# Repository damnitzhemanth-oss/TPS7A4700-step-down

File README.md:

# TPS7A4700-step-down.

## 1. Project Overview 

This is an breakout board for TPS7A4700 module. 

### How it works?

This module contains several pins like 6V2,0V2,0V4.., when connected to GND it adds the respective voltage to the OUT.

### Why I built this?

When I was designing [FusionBoard](https://github.com/damnitzhemanth-oss/FusionBoard), I was really fascinated with this board. And I wanted to design a breakout board for this.

## 2. Specifications 

| Parameter | TPS7A4700 |
|---|---:|
| Device type | Positive high-voltage, ultralow-noise LDO linear regulator |
| Input voltage range | +3 V to +36 V |
| Recommended operating input voltage | 3.0 V to 35.0 V |
| Output voltage mode | ANY-OUT user-programmable via PCB layout |
| Output voltage range | +1.4 V to +20.5 V |
| Adjustable output mode | Not applicable |
| Output current | 1 A |
| Output voltage step size | 100 mV |
| Reference voltage | 1.4 V |
| Dropout voltage | 307 mV at 1 A |
| Output noise | 4 µV_RMS (10 Hz to 100 kHz) |
| PSRR | 82 dB at 100 Hz; ≥55 dB (10 Hz to 10 MHz) |
| Enable pin | CMOS logic-level compatible |
| Protection | Built-in fixed current limit and thermal shutdown |
| Thermal shutdown temperature | ~170°C shutdown; ~150°C reset |
| Operating junction temperature | -40°C to 125°C |
| Package | VQFN-20, 5 mm × 5 mm |

Checkout [Datasheet](Datasheets/TPS7A4700.pdf) for more details.

### Pin Setting

| Vo (V) | 0P1V<br>100 mV | 0P2V<br>200 mV | 0P4V<br>400 mV | 0P8V<br>800 mV | 1P6V<br>1.6 V | 3P2V<br>3.2 V | 6P4V1<br>6.4 V | 6P4V2<br>6.4 V |
| :---: | :---: | :---: | :---: | :---: | :---: | :---: | :---: | :---: |
| 1.4 | Open | Open | Open | Open | Open | Open | Open | Open |
| 1.5 | GND | Open | Open | Open | Open | Open | Open | Open |
| 1.8 | Open | Open | GND | Open | Open | Open | Open | Open |
| 2.5 | GND | GND | Open | GND | Open | Open | Open | Open |
| 3 | Open | Open | Open | Open | GND | Open | Open | Open |
| 3.3 | GND | GND | Open | Open | GND | Open | Open | Open |
| 4.5 | GND | GND | GND | GND | GND | Open | Open | Open |
| 5 | Open | Open | GND | Open | Open | GND | Open | Open |
| 10 | Open | GND | GND | Open | GND | Open | GND | Open |
| 12 | Open | GND | Open | GND | Open | GND | GND | Open |
| 15 | Open | Open | Open | GND | Open | Open | GND | GND |
| 18 | Open | GND | GND | Open | Open | GND | GND | GND |
| 20.5 | GND | GND | GND | GND | GND | GND | GND | GND |

## 3. Bill of Materials (BoM)

| Id | Designator | Footprint | Quantity | Designation | Supplier and ref |
|---|---|---|---|---|---|
| 1 | C1, C2 | C_0805_2012Metric | 2 | 10uF | |
| 2 | C3 | C_0805_2012Metric | 1 | 47uF | |
| 3 | J1 | PinHeader_1x02_P2.54mm_Vertical | 1 | Ground/Power | |
| 4 | J2 | PinHeader_1x02_P2.54mm_Vertical | 1 | 6P4V2 | |
| 5 | J3 | PinHeader_1x02_P2.54mm_Vertical | 1 | 6P4V1 | |
| 6 | J4 | PinHeader_1x02_P2.54mm_Vertical | 1 | 3P2V | |
| 7 | J5 | PinHeader_1x02_P2.54mm_Vertical | 1 | 1P6V | |
| 8 | J6 | PinHeader_1x02_P2.54mm_Vertical | 1 | 0P8V | |
| 9 | J7 | PinHeader_1x02_P2.54mm_Vertical | 1 | 0P4V | |
| 10 | J8 | PinHeader_1x02_P2.54mm_Vertical | 1 | 0P1V | |
| 11 | J9 | PinHeader_1x02_P2.54mm_Vertical | 1 | 0PV2 | |
| 12 | OUT + 1 | PinHeader_1x01_P2.54mm_Vertical | 1 | Out Pin | |
| 13 | TP1 | TestPoint_Pad_D1.5mm | 1 | + Pad | |
| 14 | TP2 | TestPoint_Pad_D1.5mm | 1 | Ground Pad | |
| 15 | TP3 | TestPoint_Pad_D1.5mm | 1 | Out Pad | |
| 16 | U1 | VQFN-20_L5.0-W5.0-P0.65-TL-EP | 1 | TPS7A4700RGWR | |

Check [Interactive-BOM](Production/BOM/ibom.html) for more insights.

## 4. Repo Navigation

```
TPS7A4700-step-down
├── CAD
│   └── STEP_DOWN.step
├── Datasheets
│   └── TPS7A4700.pdf
├── Images
│   ├── DRC.png
│   ├── PCB3D.png
│   ├── PCB_H.png
│   └── Pin_Settings.png
├── LICENSE
├── Production
│   ├── BOM
│   │   ├── STEP_DOWN.csv
│   │   └── ibom.html
│   ├── Gerbers
│   │   ├── STEP_DOWN_47.99x31.08mm_for_Default.zip
│   │   ├── STEP_DOWN_47.99x31.08mm_for_Elecrow.zip
│   │   ├── STEP_DOWN_47.99x31.08mm_for_FusionPCB.zip
│   │   ├── STEP_DOWN_47.99x31.08mm_for_JLCPCB.zip
│   │   └── STEP_DOWN_47.99x31.08mm_for_PCBWay.zip
│   └── STEP_DOWN-all-pos.csv
├── README.md
└── STEP_DOWN
    ├── STEP_DOWN.kicad_pcb
    ├── STEP_DOWN.kicad_pro
    └── STEP_DOWN.kicad_sch
```

## 5. Credits 

- [KiCad](https://www.google.com/url?opi=89978449&q=https://www.kicad.org/&sa=U&ved=2ahUKEwimlZP32eWXAxW-jOEIHdIBCzUQFnoECBEQAQ&usg=AOvVaw3RWTRyOBHwgJWf9Tp2GrV8), used as cad.
- [easyeda2kicad](https://github.com/BiggiePete/easyeda2kicad-App) extension for downloading footprint,symbols, 3d models.
- Interactive BOM Plugin.
- Round Corners Plugin.

## 7. Gallery

### PCB 

### 3D

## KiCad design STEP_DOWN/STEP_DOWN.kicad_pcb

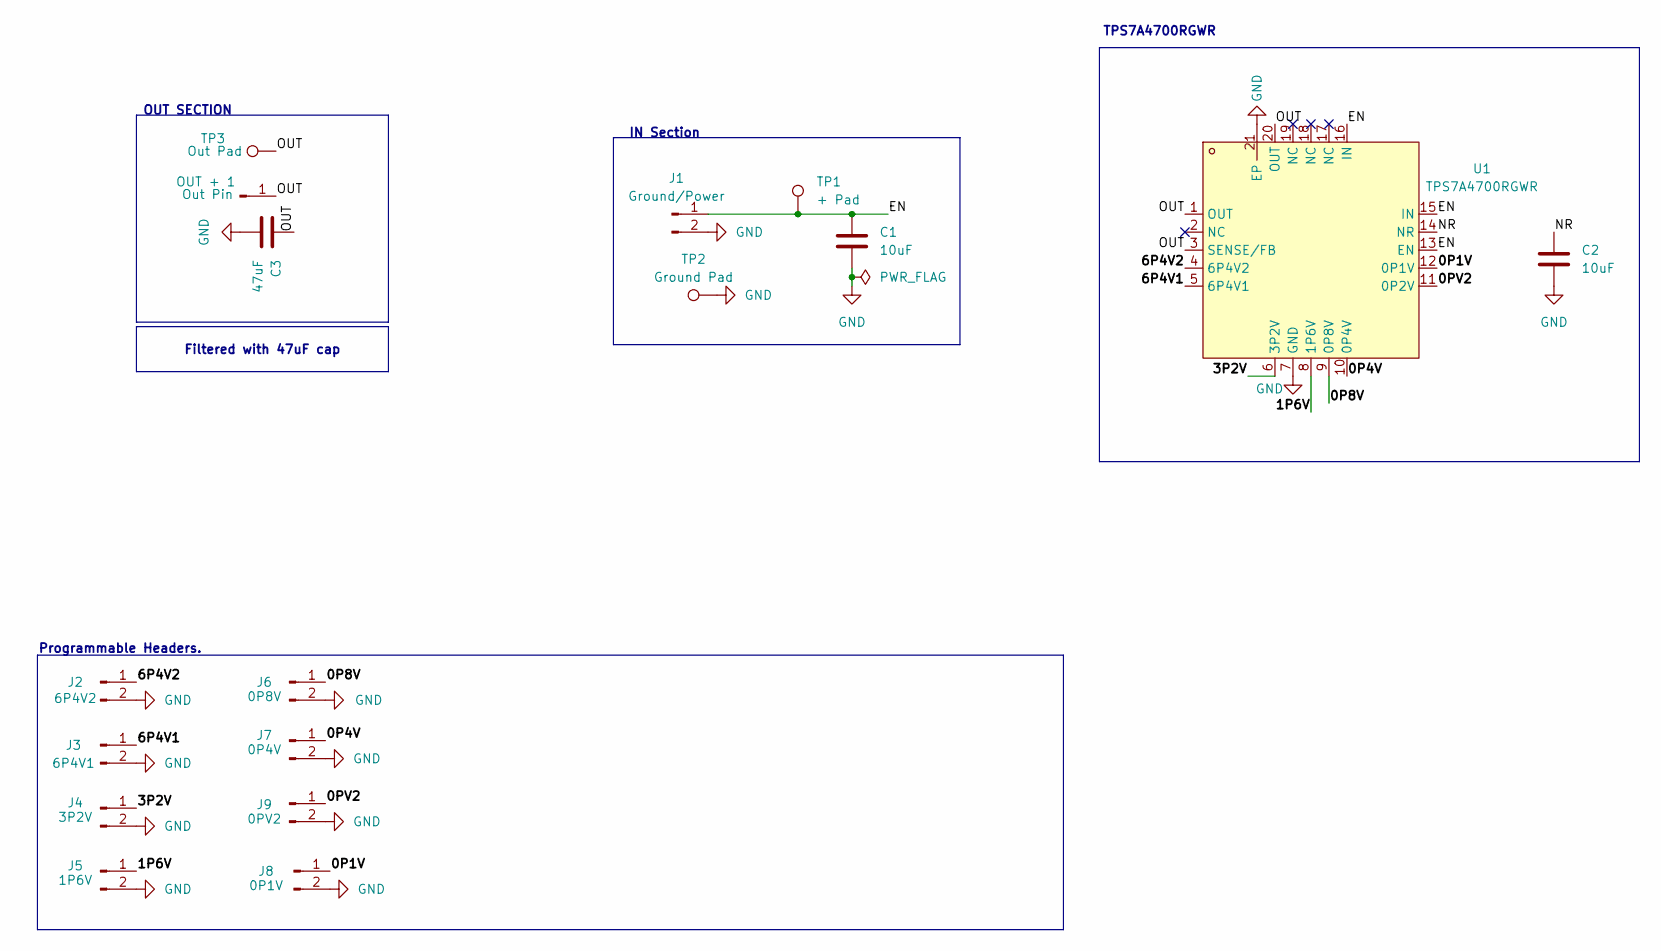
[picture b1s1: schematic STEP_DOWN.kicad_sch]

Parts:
C1, C2: 10uF; C_0805_2012Metric
C3: 47uF; C_0805_2012Metric
J1: Ground/Power; PinHeader_1x02_P2.54mm_Vertical
J2: 6P4V2; PinHeader_1x02_P2.54mm_Vertical
J3: 6P4V1; PinHeader_1x02_P2.54mm_Vertical
J4: 3P2V; PinHeader_1x02_P2.54mm_Vertical
J5: 1P6V; PinHeader_1x02_P2.54mm_Vertical
J6: 0P8V; PinHeader_1x02_P2.54mm_Vertical
J7: 0P4V; PinHeader_1x02_P2.54mm_Vertical
J8: 0P1V; PinHeader_1x02_P2.54mm_Vertical
J9: 0PV2; PinHeader_1x02_P2.54mm_Vertical
OUT + 1: Out Pin; PinHeader_1x01_P2.54mm_Vertical
TP1: + Pad; TestPoint_Pad_D1.5mm
TP2: Ground Pad; TestPoint_Pad_D1.5mm
TP3: Out Pad; TestPoint_Pad_D1.5mm
U1: TPS7A4700RGWR; VQFN-20_L5.0-W5.0-P0.65-TL-EP; MPN TPS7A4700RGWR; LCSC Part C114839

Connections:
/0P1V: J8.1, U1.12 (0P1V)
/0P4V: J7.1, U1.10 (0P4V)
/0P8V: J6.1, U1.9 (0P8V)
/0PV2: J9.1, U1.11 (0P2V)
/1P6V: J5.1, U1.8 (1P6V)
/3P2V: J4.1, U1.6 (3P2V)
/6P4V1: J3.1, U1.5 (6P4V1)
/6P4V2: J2.1, U1.4 (6P4V2)
/EN: C1.1, J1.1, TP1.1 (1_1), U1.13 (EN), U1.15 (IN), U1.16 (IN)
/NR: C2.1, U1.14 (NR)
/OUT: C3.1, OUT + 1.1 (Pin_1_1), TP3.1 (1_1), U1.1 (OUT), U1.3 (SENSE/FB), U1.20 (OUT)
GND: C1.2, C2.2, C3.2, J1.2, J2.2, J3.2, J4.2, J5.2, J6.2, J7.2, J8.2, J9.2, TP2.1 (1_1), U1.7 (GND), U1.21 (EP)

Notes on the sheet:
Programmable Headers.
IN Section
TPS7A4700RGWR
OUT SECTION
Filtered with 47uF cap

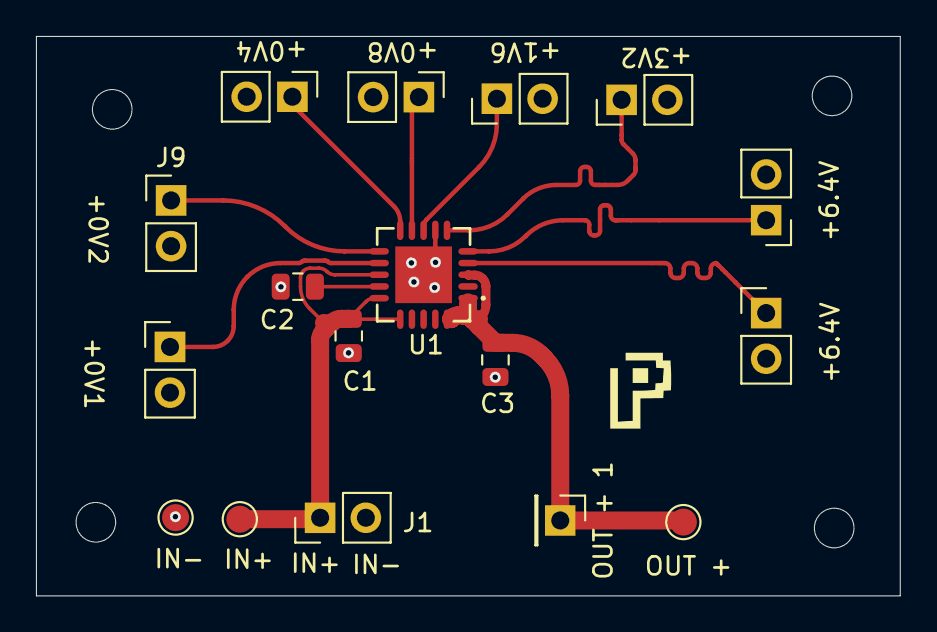
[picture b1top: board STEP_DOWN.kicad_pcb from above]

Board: 2 copper layers, 48.0 x 31.1 mm, 17 parts (0 on the bottom side), 12 nets.
